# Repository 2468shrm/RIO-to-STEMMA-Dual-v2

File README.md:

# RIO-to-STEMMA-Dual-v2

This board allows for STEMMA QT / Qwiic sensors to be easily added to a
roboRIO. The PCB includes a screw mount for more secure connection. Two
STEMMA QT connectors are provided, one facing towards the roboRIO power
input and one opposite.

## Disclaimer

This board has NOT yet been fabricated and mechanically verified. I've
done my best to check this in CAD. However, there could be small issues
yet to be discovered. Use at own risk.

Why did I publish before fabricating you ask? FRC rules which would not
allow the prototype to be used on a competition robot if the board is
made prior to Kickoff. This makes for e-waste (IMO). This board will be
sent to fab after Kickoff and updates will be made if needed.

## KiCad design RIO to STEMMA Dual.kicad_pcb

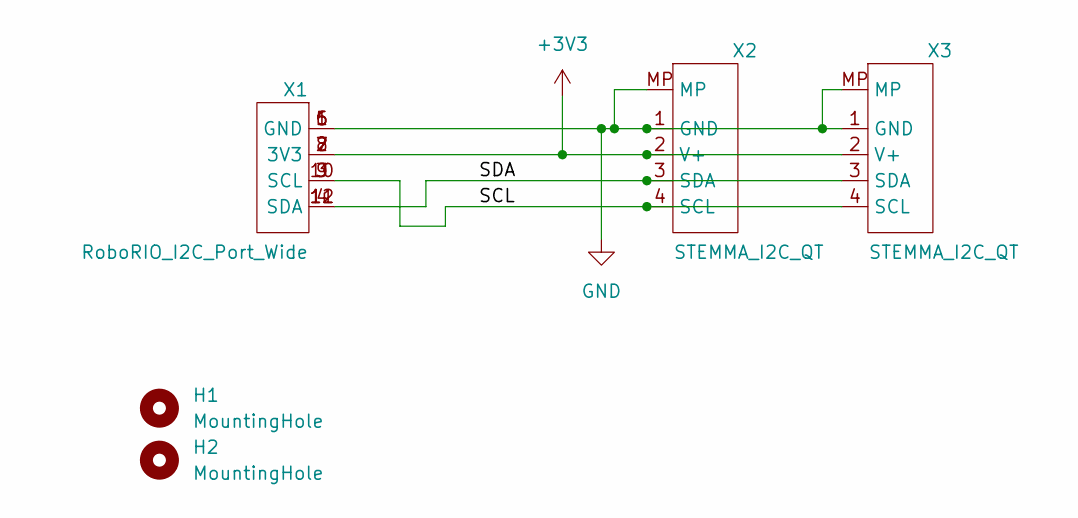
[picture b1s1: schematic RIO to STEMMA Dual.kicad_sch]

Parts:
H1, H2: MountingHole; MountingHole_2.2mm_M2_ISO7380_Pad
X1: RoboRIO_I2C_Port_Wide
X2, X3: STEMMA_I2C_QT; JST_SH_SM04B-SRSS-TB_1x04-1MP_P1.00mm_Horizontal

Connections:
+3V3: X1.2 (3V3), X1.7 (3V3), X1.8 (3V3), X2.2 (V+), X3.2 (V+)
/SCL: X1.3 (SCL), X1.9 (SCL), X1.10 (SCL), X2.4 (SCL), X3.4 (SCL)
/SDA: X1.4 (SDA), X1.11 (SDA), X1.12 (SDA), X2.3 (SDA), X3.3 (SDA)
GND: X1.1 (GND), X1.5 (GND), X1.6 (GND), X2.1 (GND), X2.MP, X3.1 (GND), X3.MP

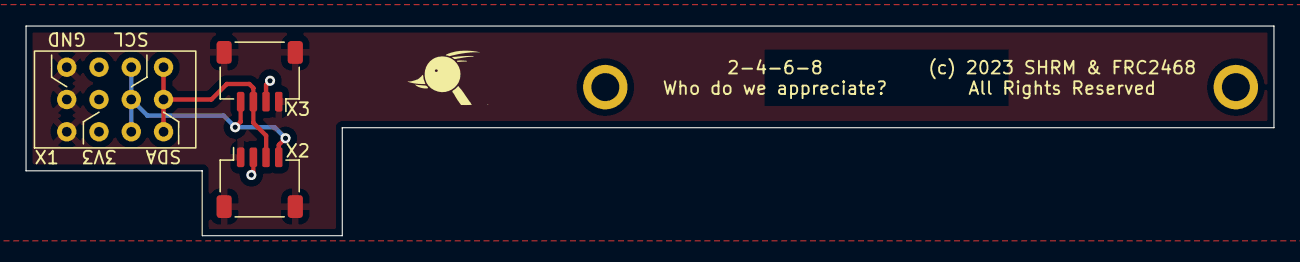
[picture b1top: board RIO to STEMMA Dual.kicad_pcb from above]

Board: 2 copper layers, 98.2 x 16.5 mm, 5 parts (1 on the bottom side), 4 nets.

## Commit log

2024-01-03 PCB files
2024-01-03 adding CAD model
2024-01-03 updated docs
2024-01-06 added images for docs
2024-01-06 updated iso image
2024-01-06 updated docs to show image
2024-01-06 added manufacturing files (Gerbers)

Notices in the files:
RIO to STEMMA Dual.kicad_pcb:
(c) 2023 SHRM & FRC2468
All Rights Reserved
